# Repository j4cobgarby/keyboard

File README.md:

# My keyboard

Here's the CAD files and the firmware (which isn't yet written) for a keyboard I'm making.

I'm using KiCAD to create the schematic and PCB design.

I'm using an ATmega32u4 microcontroller to send data to the computer.

## Schematic:

## Renders

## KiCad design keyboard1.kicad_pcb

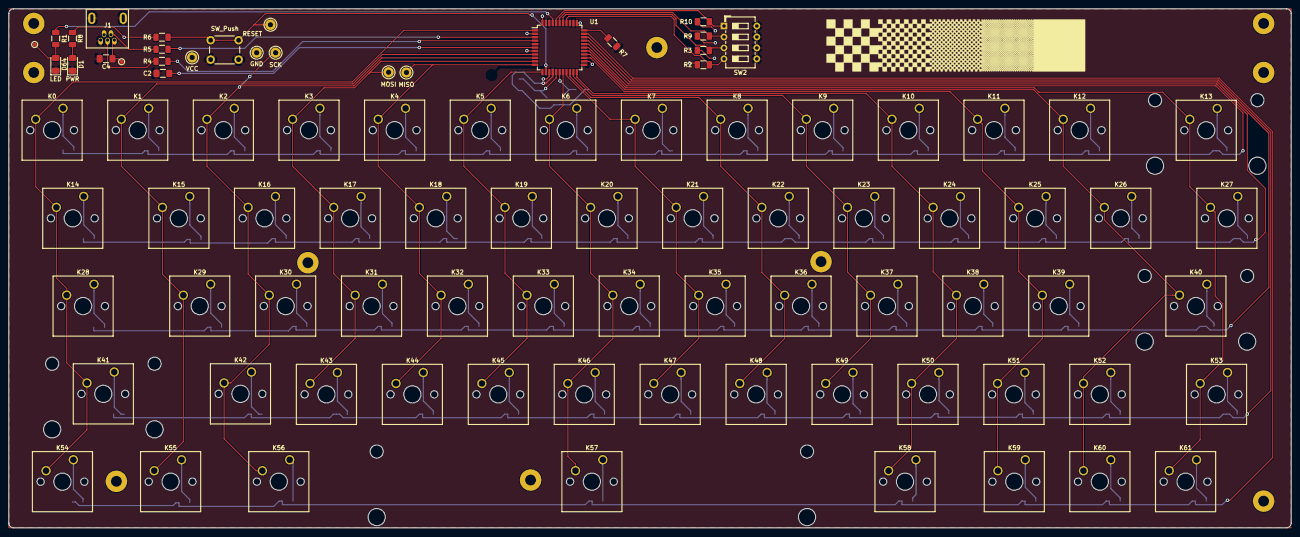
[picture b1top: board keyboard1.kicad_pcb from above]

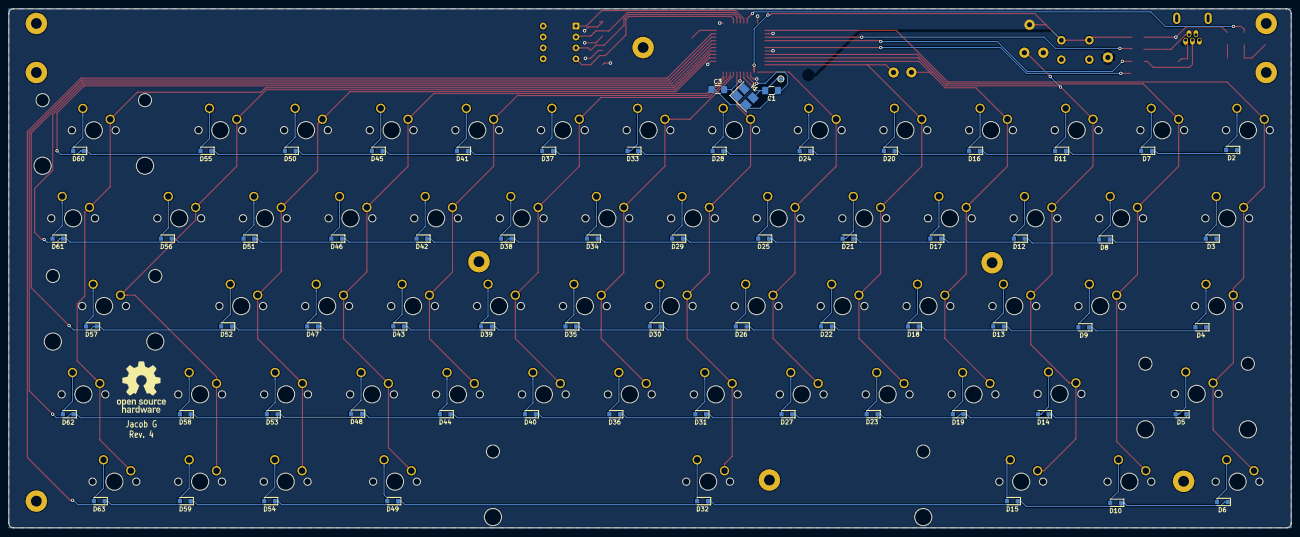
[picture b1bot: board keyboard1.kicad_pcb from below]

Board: 2 copper layers, 298.0 x 120.6 mm, 154 parts (66 on the bottom side), 99 nets.

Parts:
C1, C3: 22p; C_1206_3216Metric_Pad1.42x1.75mm_HandSolder
C2: 1u; C_1206_3216Metric_Pad1.42x1.75mm_HandSolder
C4: 10uF; C_1206_3216Metric_Pad1.42x1.75mm_HandSolder
D1: PWR; LED_1206_3216Metric_Pad1.42x1.75mm_HandSolder
D2, D3, D4, D5, D6, D7, D8, D9, D10, D11, D12, D13, D14, D15, D16, D17, D18, D19, D20, D21, D22, D23, D24, D25, D26, D27, D28, D29, D30, D31, D32, D33, D34, D35, D36, D37, D38, D39, D40, D41, D42, D43, D44, D45, D46, D47, D48, D49, D50, D51, D52, D53, D54, D55, D56, D57, D58, D59, D60, D61, D62, D63: DIODE; D_SOD-323_HandSoldering
D64: LED; LED_1206_3216Metric_Pad1.42x1.75mm_HandSolder
J1: USB_B_Mini; Molex_OTG_54819_Right_angle
J2: GND; Pin_D1.0mm_L10.0mm_LooseFit
J3: VCC; Pin_D1.0mm_L10.0mm_LooseFit
J4: SCK; Pin_D1.0mm_L10.0mm_LooseFit
J5: MOSI; Pin_D1.0mm_L10.0mm_LooseFit
J6: MISO; Pin_D1.0mm_L10.0mm_LooseFit
J7: RESET; Pin_D1.0mm_L10.0mm_LooseFit
K0, K1, K2, K3, K4, K5, K6, K7, K8, K9, K10, K11, K12, K15, K16, K17, K18, K19, K20, K21, K22, K23, K24, K25, K26, K29, K30, K31, K32, K33, K34, K35, K36, K37, K38, K39, K42, K43, K44, K45, K46, K47, K48, K49, K50, K51, K52, K59, K60, K61: SW_Push; SW_Cherry_MX1A_1.00u_PCB
K13: SW_Push; SW_Cherry_MX1A_2.00u_PCB
K14, K27: SW_Push; SW_Cherry_MX1A_1.50u_PCB
K28, K53: SW_Push; SW_Cherry_MX1A_1.75u_PCB
K40, K41: SW_Push; SW_Cherry_MX1A_2.25u_PCB
K54, K55, K56, K58: SW_Push; SW_Cherry_MX1A_1.25u_PCB
K57: SW_Push; SW_Cherry_MX1A_6.25u_PCB
R1: 330; R_1206_3216Metric
R2, R3, R9, R10: 1k; R_1206_3216Metric
R4, R5: 22; R_1206_3216Metric
R6, R7: 10k; R_1206_3216Metric
R8: 300; R_1206_3216Metric
SW1: SW_Push; SW_PUSH_6mm_H4.3mm
SW2: SW_DIP_x04; SW_DIP_SPSTx04_Slide_6.7x11.72mm_W7.62mm_P2.54mm_LowProfile
TP1, TP2, TP3: TestPoint_Probe; TestPoint_Pad_D1.0mm
U1: ATmega32U4-AU; TQFP-44_10x10mm_P0.8mm
Y1: 16MHz; Crystal_SMD_3225-4Pin_3.2x2.5mm_HandSoldering

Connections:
/DIP1: R10.1, SW2.1, U1.40
/DIP2: R9.1, SW2.2, U1.39
/DIP3: R3.1, SW2.3, U1.38
/DIP4: R2.1, SW2.4, U1.37
/LED: R1.2, U1.41
/ROW0: D2.1, D7.1, D11.1, D16.1, D20.1, D24.1, D28.1, D33.1, D37.1, D41.1, D45.1, D50.1, D55.1, D60.1, U1.28
/ROW1: D3.1, D8.1, D12.1, D17.1, D21.1, D25.1, D29.1, D34.1, D38.1, D42.1, D46.1, D51.1, D56.1, D61.1, U1.29
/ROW2: D4.1, D9.1, D13.1, D18.1, D22.1, D26.1, D30.1, D35.1, D39.1, D43.1, D47.1, D52.1, D57.1, U1.30
/ROW3: D5.1, D14.1, D19.1, D23.1, D27.1, D31.1, D36.1, D40.1, D44.1, D48.1, D53.1, D58.1, D62.1, U1.31
/ROW4: D6.1, D10.1, D15.1, D32.1, D49.1, D54.1, D59.1, D63.1, U1.32
/RST: J7.1, R6.2, SW1.2, U1.13
/col0: K0.2, K14.2, K28.2, K41.2, K54.2, U1.1
/col1: K1.2, K15.2, K29.2, K55.2, U1.8
/col2: J4.1, K2.2, K16.2, K30.2, K42.2, K56.2, U1.9
/col3: J5.1, K3.2, K17.2, K31.2, K43.2, U1.10
/col4: J6.1, K4.2, K18.2, K32.2, K44.2, U1.11
/col5: K5.2, K19.2, K33.2, K45.2, U1.12
/col6: K6.2, K20.2, K34.2, K46.2, K57.2, U1.18
/col7: K7.2, K21.2, K35.2, K47.2, U1.19
/col8: K8.2, K22.2, K36.2, K48.2, U1.20
/col9: K9.2, K23.2, K37.2, K49.2, U1.21
/col10: K10.2, K24.2, K38.2, K50.2, K58.2, U1.22
/col11: K11.2, K25.2, K39.2, K51.2, K59.2, U1.25
/col12: K12.2, K26.2, K40.2, K52.2, K60.2, U1.26
/col13: K13.2, K27.2, K53.2, K61.2, U1.27
GND: C1.1, C2.2, C3.1, C4.2, D1.1, D64.1, J1.5, J1.6, J2.1, R7.1, SW1.1, SW2.5, SW2.6, SW2.7, SW2.8, U1.5, U1.15, U1.23, U1.35, U1.43, Y1.2
unnamed: C1.2, TP1.1, U1.16, Y1.3
unnamed: C2.1, U1.6
unnamed: C3.2, U1.17, Y1.1
unnamed: D1.2, R8.2
unnamed: D2.2, K0.1
unnamed: D3.2, K14.1
unnamed: D4.2, K28.1
unnamed: D5.2, K41.1
unnamed: D6.2, K54.1
unnamed: D7.2, K1.1
unnamed: D8.2, K15.1
unnamed: D9.2, K29.1
unnamed: D10.2, K55.1
unnamed: D11.2, K2.1
unnamed: D12.2, K16.1
unnamed: D13.2, K30.1
unnamed: D14.2, K42.1
unnamed: D15.2, K56.1
unnamed: D16.2, K3.1
unnamed: D17.2, K17.1
unnamed: D18.2, K31.1
unnamed: D19.2, K43.1
unnamed: D20.2, K4.1
unnamed: D21.2, K18.1
unnamed: D22.2, K32.1
unnamed: D23.2, K44.1
unnamed: D24.2, K5.1
unnamed: D25.2, K19.1
unnamed: D26.2, K33.1
unnamed: D27.2, K45.1
unnamed: D28.2, K6.1
unnamed: D29.2, K20.1
unnamed: D30.2, K34.1
unnamed: D31.2, K46.1
unnamed: D32.2, K57.1
unnamed: D33.2, K7.1
unnamed: D34.2, K21.1
unnamed: D35.2, K35.1
unnamed: D36.2, K47.1
unnamed: D37.2, K8.1
unnamed: D38.2, K22.1
unnamed: D39.2, K36.1
unnamed: D40.2, K48.1
unnamed: D41.2, K9.1
unnamed: D42.2, K23.1
unnamed: D43.2, K37.1
unnamed: D44.2, K49.1
unnamed: D45.2, K10.1
unnamed: D46.2, K24.1
unnamed: D47.2, K38.1
unnamed: D48.2, K50.1
unnamed: D49.2, K58.1
unnamed: D50.2, K11.1
unnamed: D51.2, K25.1
unnamed: D52.2, K39.1
unnamed: D53.2, K51.1
unnamed: D54.2, K59.1
unnamed: D55.2, K12.1
unnamed: D56.2, K26.1
unnamed: D57.2, K40.1
unnamed: D58.2, K52.1
unnamed: D59.2, K60.1
unnamed: D60.2, K13.1
unnamed: D61.2, K27.1
unnamed: D62.2, K53.1
unnamed: D63.2, K61.1
unnamed: D64.2, R1.1, TP3.1
unnamed: J1.2, R5.2
unnamed: J1.3, R4.2
unnamed: R4.1, U1.4
unnamed: R5.1, U1.3
unnamed: R7.2, U1.33
VCC: C4.1, J1.1, J3.1, R2.2, R3.2, R6.1, R8.1, R9.2, R10.2, TP2.1, U1.2, U1.7, U1.14, U1.24, U1.34, U1.44

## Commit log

2018-10-12 initial
2018-10-13 progress wiring mcu
2018-10-13 add layout
2018-10-13 finished wiring up mcu
2018-10-13 update gitignore
2018-10-13 remove cache lib
2018-10-13 added image of layout
2018-10-13 added layout image to readme
2018-10-14 finished keyboard schematic
2018-10-15 pcb progress
2018-10-15 almost finished routing
2018-10-18 finish pcb
2019-04-10 save
2019-04-16 check
2019-04-17 udpate readme
2019-04-17 add schematic
